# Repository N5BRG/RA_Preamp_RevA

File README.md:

# RA_Preamp_RevA

Copyright (c) 2026 Robert S. Stricklin Jr

This hardware design is licensed under the CERN Open Hardware Licence Version 2 - Permissive (CERN-OHL-P-2.0).

You may obtain a copy of the license in the `LICENSE` file included with this repository.

## Overview

This design is a Radio Astronomy Preamplifier intended for operation at 1420 MHz, which is approximately the frequency of the neutral hydrogen spectral line produced by the hyperfine spin-flip transition of hydrogen atoms in space. This signal is commonly referred to as the **Hydrogen Line** or the **21-centimeter Hydrogen Line**.

The goal of this preamplifier is to provide the lowest practical noise figure while amplifying extremely low-level radio signals. Included in the design is a PIN diode switch that allows switching between the antenna input and an alternate path terminated with a precision 50-ohm reference resistor. This approach is similar to the Dicke switching technique developed by [Robert H. Dicke](https://en.wikipedia.org/wiki/Robert_H._Dicke) in the mid-1940s for microwave radiometry and receiver calibration.

For best performance, the preamplifier is powered from a low-noise 5-volt power supply (5.5 V maximum). The PIN diode switch is controlled by an external voltage of approximately 1.8 to 2.5 volts applied to the control input for the ON state (3.3 V maximum), and 0 V to -20 mV for the OFF state. The analog RF ground and the digital switching ground are separated to minimize the possibility of switching noise coupling into the RF signal path.

The total current required by the preamplifier is approximately 160 mA, although this value may vary somewhat with temperature and component tolerances. At 5 volts and 160 mA, the power dissipation is approximately 800 mW at 25°C, so good thermal management should be considered when mounting the preamplifier in an enclosure.

The PCB is designed to plug into a power and control PCB. However, because the power board is longer, it may be more practical to mount the boards side-by-side if the power board is used. To minimize noise, a low-noise linear voltage regulator is recommended.

A graph showing the noise figure versus frequency, along with the gain of the preamplifier, is included with the project files. These measurements were obtained using an HP 8970B Noise Figure Meter. The 1420 MHz noise figure is 0.46 dB and the gain is 40.11 dB.

## Amateur Radio Astronomy

This design was created to support the educational and scientific goals of the Society of Amateur Radio Astronomers (SARA). Additional information about SARA can be found at:

https://www.radio-astronomy.org/

Many of the ideas incorporated into this design were discussed during SARA's regular monthly Zoom meetings and educational activities.

If you enjoy physics, astronomy, radio astronomy, electronics, and scientific experimentation, please consider joining SARA and participating in its programs. SARA is an especially good opportunity for students and young people who are interested in science, engineering, and technology. Most participation is conducted online through video conference meetings.

## Acknowledgements

If you use KiCad, please consider making a donation to the project to help support the continuing development and distribution of this outstanding open-source electronic design software.

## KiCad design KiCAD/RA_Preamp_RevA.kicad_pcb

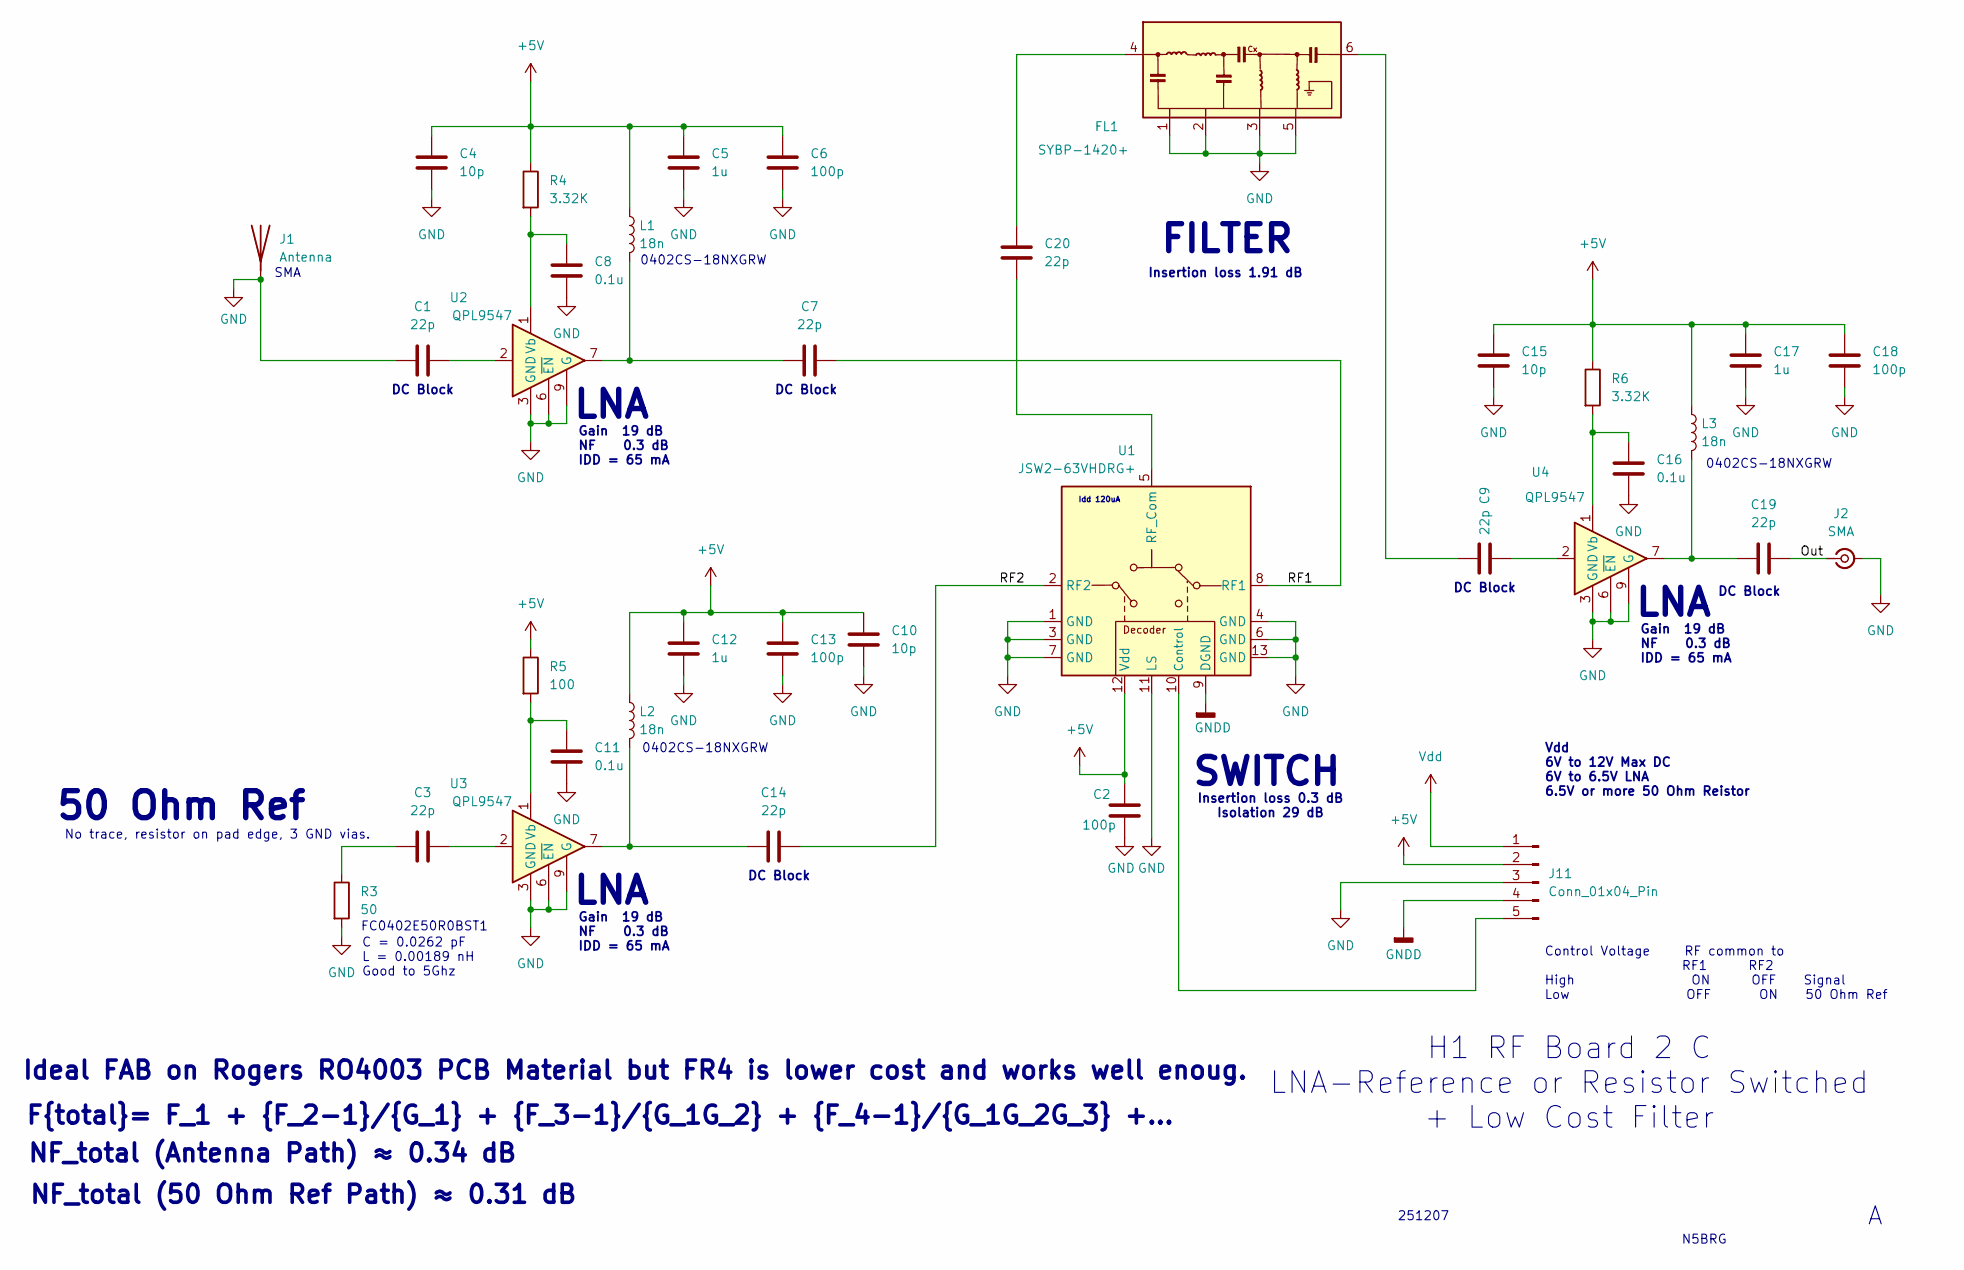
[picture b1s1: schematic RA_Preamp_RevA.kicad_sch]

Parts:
C1, C3, C7, C9, C14, C19, C20: 22p; C_0402_1005Metric; MPN 0402YK220FBWTR
C2: 100p; C_0603_1608Metric_Pad1.08x0.95mm_HandSolder; MPN GCM1555C1H101FA16J
C4, C10, C15: 10p; C_0402_1005Metric; MPN C0402C100K4RACAUTO
C5, C12, C17: 1u; C_0402_1005Metric; MPN C0402C105K4PACTU
C6, C13, C18: 100p; C_0402_1005Metric; MPN GCM1555C1H101FA16J
C8, C11, C16: 0.1u; C_0402_1005Metric; MPN CC0402KRX7R7BB104
FL1: SYBP-1420+; PL-308; MPN Do Not Populate
J1: Antenna; SMA_WIDE_GND_EdgeMount_Small; MPN SMA Connector Board Edge
J2: SMA; SMA_WIDE_GND_EdgeMount_Small; MPN TBD SMA Connector Board Edge
J11: Conn_01x04_Pin; PinSocket_1x05_P2.54mm_Vertical; MPN 1001-0-15-15-30-27-04-0 (5X)
L1, L2, L3: 18n; L_0402_1005Metric; MPN 0402CS-18NXGRW
R3: 50; R_0402_1005Metric; MPN FC0402E50R0BST1
R4, R6: 3.32K; R_0402_1005Metric; MPN RC0402JR-073K3L
R5: 100; R_0402_1005Metric; MPN RC0402JR-073K3L
U1: JSW2-63VHDRG+; MT2140_With_polygons_custompads; MPN JSW2-63VHDRG+
U2, U3, U4: QPL9547; DFN-8-1EP_2x2mm_P0.5mm_EP0.8x1.6mm; MPN QPL9547TR7

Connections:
+5V: C2.2, C4.2, C5.2, C6.2, C10.2, C12.2, C13.2, C15.2, C17.2, C18.2, J11.2, L1.1, L2.1, L3.1, R4.1, R5.1, R6.1, U1.12 (Vdd)
/Out: C19.2, J2.1 (In)
/RF1: C7.2, U1.8 (RF1)
/RF2: C14.2, U1.2 (RF2)
GND: C1.1, C2.1, C4.1, C5.1, C6.1, C8.1, C10.1, C11.1, C12.1, C13.1, C15.1, C16.1, C17.1, C18.1, FL1.1 (GND), FL1.2 (GND), FL1.3 (GND), FL1.5 (GND), J1.1 (A_1), J2.2 (Ext), J11.3, R3.2, U1.1 (GND), U1.3 (GND), U1.4 (GND), U1.6 (GND), U1.7 (GND), U1.11 (LS), U1.13 (GND), U2.3 (GND), U2.4 (GND), U2.5 (GND), U2.6 (~EN), U2.8 (GND), U2.9 (GND), U3.3 (GND), U3.4 (GND), U3.5 (GND), U3.6 (~EN), U3.8 (GND), U3.9 (G), U4.3 (GND), U4.4 (GND), U4.5 (GND), U4.6 (~EN), U4.8 (GND), U4.9 (GND); also elsewhere on the board
GNDD: J11.4, U1.9 (DGND)
unnamed: C1.2, U2.2
unnamed: C3.1, R3.1
unnamed: C3.2, U3.2
unnamed: C7.1, L1.2, U2.7
unnamed: C9.1, FL1.6
unnamed: C9.2, U4.2
unnamed: C14.1, L2.2, U3.7
unnamed: C19.1, L3.2, U4.7
unnamed: C20.2, FL1.4
unnamed: J11.5, U1.10 (Control)
unnamed: C20.1, U1.5 (RF_Com)
unnamed: C8.2, R4.2, U2.1 (Vb)
unnamed: C11.2, R5.2, U3.1 (Vb)
unnamed: C16.2, R6.2, U4.1 (Vb)
Vdd: J11.1

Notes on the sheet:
F{total}= F_1 + {F_2-1}/{G_1} + {F_3-1}/{G_1G_2} + {F_4-1}/{G_1G_2G_3} +...
FILTER
N5BRG
0402CS-18NXGRW
DC Block
LNA
251207
FC0402E50R0BST1
Gain 19 dB NF 0.3 dB IDD = 65 mA
NF_total (50 Ohm Ref Path) ≈ 0.31 dB
SMA
No trace, resistor on pad edge, 3 GND vias.
Vdd 6V to 12V Max DC 6V to 6.5V LNA 6.5V or more 50 Ohm Reistor
Idd 120uA
50 Ohm Ref
Insertion loss 1.91 dB
Insertion loss 0.3 dB Isolation 29 dB
NF_total (Antenna Path) ≈ 0.34 dB
C = 0.0262 pF L = 0.00189 nH Good to 5Ghz
SWITCH
H1 RF Board 2 C LNA-Reference or Resistor Switched + Low Cost Filter
Ideal FAB on Rogers RO4003 PCB Material but FR4 is lower cost and works well enoug.
Control Voltage RF common to RF1 RF2 High ON OFF Signal Low OFF ON 50 Ohm Ref

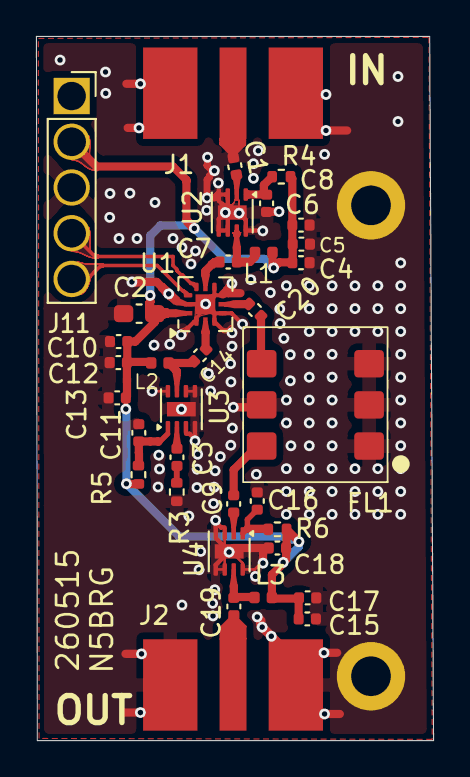
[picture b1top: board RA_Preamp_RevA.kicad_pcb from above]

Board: 2 copper layers, 22.1 x 39.1 mm, 37 parts (0 on the bottom side), 20 nets.

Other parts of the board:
H10, H11: MountingHole_Pad; MountingHole_2.2mm_M2_DIN965_Pad

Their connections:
GND: H10.1 (1_1), H11.1 (1_1); also elsewhere on the board

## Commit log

2026-06-07 Initial posting
2026-06-07 Rename README for GitHub
2026-06-07 Remove temporary files and add gitignore
2026-06-07 Fix file permissions
